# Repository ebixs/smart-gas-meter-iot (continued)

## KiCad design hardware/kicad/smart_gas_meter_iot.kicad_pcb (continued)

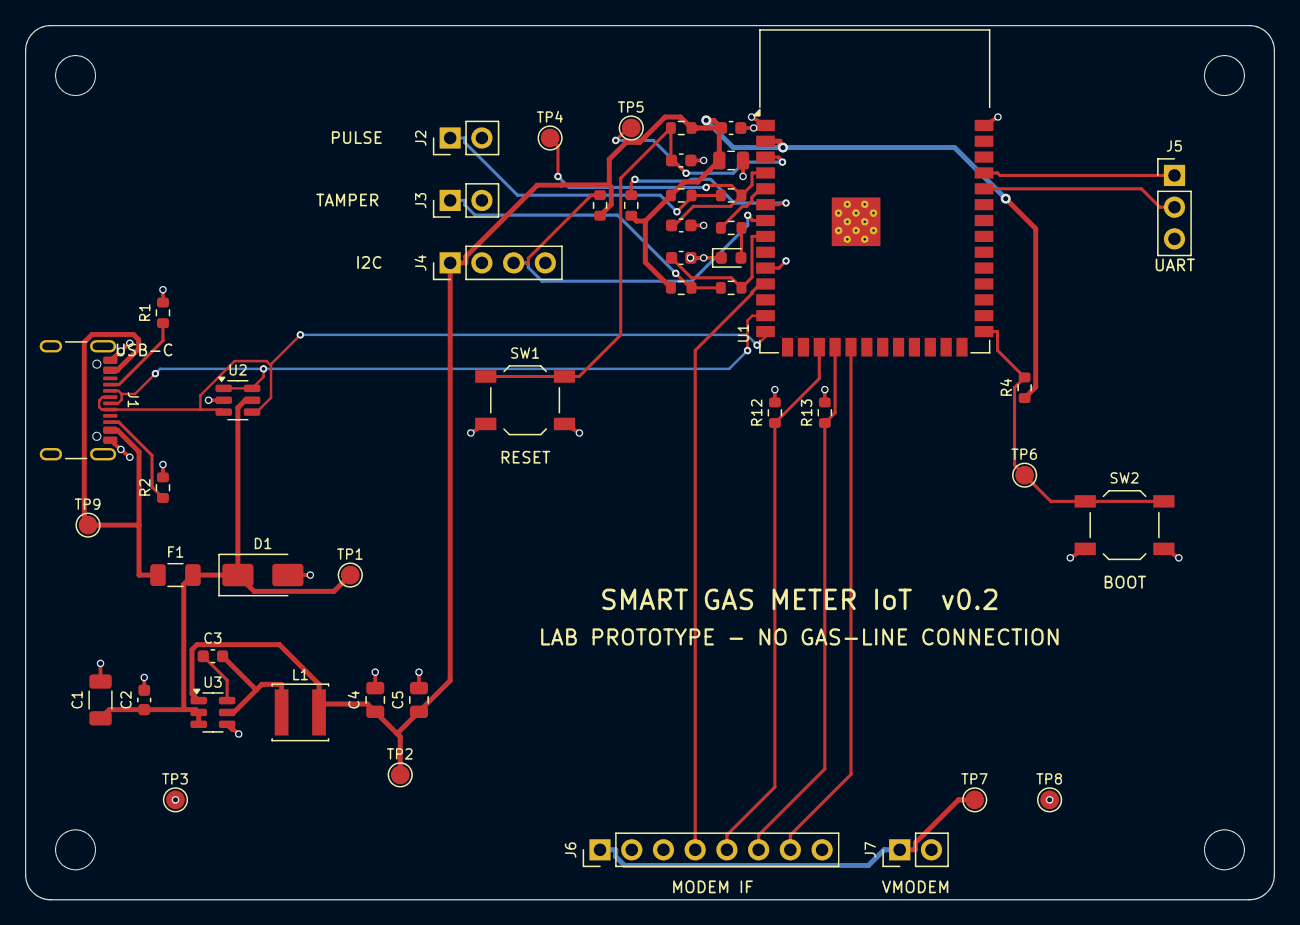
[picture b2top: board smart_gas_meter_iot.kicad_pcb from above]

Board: 4 copper layers, 100.0 x 70.0 mm, 52 parts (0 on the bottom side), 28 nets.

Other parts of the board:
H1, H2, H3, H4: M3; MountingHole_3.2mm_M3

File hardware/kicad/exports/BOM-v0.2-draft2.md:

# BOM — carrier board v0.2-draft2 (generated from `design_v02.py`)

**Candidate BOM — not approved for purchase.** `TBD` / `candidate` entries must be selected and checked against datasheets before freeze.

| Ref | Value | Footprint (SGM lib) | MPN / status | DNP | Note |
|---|---|---|---|---|---|
| J1 | USB-C receptacle (USB 2.0, sink) | `USB_C_Receptacle_GCT_USB4105-xx-A_16P_TopMnt_Horizontal` | GCT USB4105-GF-A (candidate) |  | Footprint/pin map must be checked against the selected connector drawing |
| R1 | 5.1k 1% | `R_0603_1608Metric` | TBD |  | USB-C sink Rd on CC1 |
| R2 | 5.1k 1% | `R_0603_1608Metric` | TBD |  | USB-C sink Rd on CC2 |
| F1 | PTC 0.75A hold, >=6V | `Fuse_1206_3216Metric` | TBD |  | Resettable input protection; size after load budget |
| D1 | TVS 5V standoff (candidate SMAJ5.0CA) | `D_SMA` | SMAJ5.0CA (candidate) |  | VBUS surge clamp after the fuse |
| U2 | USBLC6-2SC6 | `SOT-23-6` | STMicroelectronics USBLC6-2SC6 |  | Low-capacitance USB ESD array; place at the connector |
| U3 | AP63203WU-7 (3.3V buck) | `TSOT-23-6` | Diodes Inc. AP63203WU-7 |  | Fixed 3.3V: FB senses the output; EN tied to VIN (datasheet: auto start-up) |
| C1 | 10uF 25V X7R | `C_1206_3216Metric` | TBD |  | Buck input capacitor (datasheet CIN) |
| C2 | 100nF 50V | `C_0603_1608Metric` | TBD |  | High-frequency input bypass, close to VIN |
| C3 | 100nF 25V | `C_0603_1608Metric` | TBD |  | Bootstrap capacitor between BST and SW (datasheet CBST) |
| L1 | 3.9uH, Isat>=3A (candidate) | `L_Taiyo-Yuden_NR-40xx` | TBD |  | Datasheet table value for 3.3V output |
| C4 | 22uF 10V X7R | `C_0805_2012Metric` | TBD |  | Buck output capacitor 1/2 (datasheet 2x22uF) |
| C5 | 22uF 10V X7R | `C_0805_2012Metric` | TBD |  | Buck output capacitor 2/2 |
| U1 | ESP32-S3-WROOM-1-N8 | `ESP32-S3-WROOM-1` | Espressif ESP32-S3-WROOM-1-N8 |  | Pin numbers per KiCad RF_Module symbol = Espressif datasheet pin table |
| C6 | 10uF 10V X7R | `C_0805_2012Metric` | TBD |  | Module bulk decoupling at the 3V3 pin |
| C7 | 100nF 16V | `C_0603_1608Metric` | TBD |  | Module HF decoupling at the 3V3 pin |
| R3 | 10k | `R_0603_1608Metric` | TBD |  | EN pull-up (Espressif RC delay R=10k) |
| C8 | 1uF 16V | `C_0603_1608Metric` | TBD |  | EN delay capacitor (Espressif RC delay C=1uF) |
| SW1 | RESET | `SW_SPST_TL3342` | TBD |  | Pulls EN low to reset |
| R4 | 10k | `R_0603_1608Metric` | TBD |  | GPIO0 strapping pull-up (run from flash by default) |
| SW2 | BOOT | `SW_SPST_TL3342` | TBD |  | Hold during reset for USB download mode |
| J2 | PULSE_IN (synthetic 3.3V lab signal only) | `PinHeader_1x02_P2.54mm_Vertical` | TBD |  | Max 3.3V logic or dry contact to GND. Never connect a live meter or field wiring |
| R5 | 10k | `R_0603_1608Metric` | TBD |  | Defined idle-high state / dry-contact pull-up |
| R6 | 1k | `R_0603_1608Metric` | TBD |  | Series current limit; place near the MCU pin |
| C9 | 100nF (DNP) | `C_0603_1608Metric` | TBD | yes | Optional RC filter footprint, not fitted by default |
| R7 | 1k | `R_0603_1608Metric` | TBD |  | ~1.3mA with a 2V LED; adjust after LED selection |
| D2 | Green LED | `LED_0603_1608Metric` | TBD |  | Active-high status LED (pin 2 = anode) |
| J3 | TAMPER switch | `PinHeader_1x02_P2.54mm_Vertical` | TBD |  | Enclosure switch closed to GND when lid is closed; open = tamper (advisory only) |
| R8 | 10k | `R_0603_1608Metric` | TBD |  | Pull-up: wire break or lid open reads high |
| R9 | 1k | `R_0603_1608Metric` | TBD |  | Series resistor |
| C10 | 100nF | `C_0603_1608Metric` | TBD |  | Debounce (~1ms with R9) |
| J4 | I2C expansion (3.3V) | `PinHeader_1x04_P2.54mm_Vertical` | TBD |  | Optional 3.3V I2C sensors |
| R10 | 4.7k | `R_0603_1608Metric` | TBD |  | I2C pull-up |
| R11 | 4.7k | `R_0603_1608Metric` | TBD |  | I2C pull-up |
| J5 | Debug UART0 (3.3V) | `PinHeader_1x03_P2.54mm_Vertical` | TBD |  | Pin 1 = module TXD0 output; no power pin to avoid back-feeding |
| J6 | Modem daughterboard interface | `PinHeader_1x08_P2.54mm_Vertical` | TBD |  | 3.3V logic interface; daughterboard provides level translation and modem power design |
| J7 | MODEM_VIN bench supply input | `PinHeader_1x02_P2.54mm_Vertical` | TBD |  | Separate current-limited supply sized to the selected modem; never from +3V3 |
| R12 | 100k | `R_0603_1608Metric` | TBD |  | Modem held disabled while MCU boots |
| R13 | 100k | `R_0603_1608Metric` | TBD |  | Reset de-asserted by default (polarity per modem) |
| TP1 | TP_5V | `TestPoint_Pad_D1.5mm` | TBD |  |  |
| TP2 | TP_3V3 | `TestPoint_Pad_D1.5mm` | TBD |  |  |
| TP3 | TP_GND | `TestPoint_Pad_D1.5mm` | TBD |  |  |
| TP4 | TP_PULSE | `TestPoint_Pad_D1.5mm` | TBD |  |  |
| TP5 | TP_EN | `TestPoint_Pad_D1.5mm` | TBD |  |  |
| TP6 | TP_BOOT | `TestPoint_Pad_D1.5mm` | TBD |  |  |
| TP7 | TP_VMODEM | `TestPoint_Pad_D1.5mm` | TBD |  |  |
| TP8 | TP_GND2 | `TestPoint_Pad_D1.5mm` | TBD |  |  |
| TP9 | TP_VBUS | `TestPoint_Pad_D1.5mm` | TBD |  |  |

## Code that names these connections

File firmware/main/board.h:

/*
 * GPIO map of the v0.2 board (hardware/kicad/design_v02.py, U1 = ESP32-S3-WROOM-1).
 * Module pin -> GPIO per the Espressif WROOM-1 datasheet pin table.
 * tests/test_firmware_core.py checks this file against the design source.
 */
#ifndef SGM_BOARD_H
#define SGM_BOARD_H

#include "driver/gpio.h"

#define SGM_GPIO_PULSE_IN      GPIO_NUM_4   /* module pin 4,  net PULSE_IN (10k pull-up, 1k series) */
#define SGM_GPIO_LED           GPIO_NUM_5   /* module pin 5,  net LED_DRV (active high) */
#define SGM_GPIO_I2C_SDA       GPIO_NUM_6   /* module pin 6,  net I2C_SDA */
#define SGM_GPIO_I2C_SCL       GPIO_NUM_7   /* module pin 7,  net I2C_SCL */
#define SGM_GPIO_TAMPER_IN     GPIO_NUM_15  /* module pin 8,  net TAMPER_IN (high = lid open / wire cut) */
#define SGM_GPIO_MODEM_TXD     GPIO_NUM_17  /* module pin 10, net MODEM_TXD (MCU -> modem) */
#define SGM_GPIO_MODEM_RXD     GPIO_NUM_18  /* module pin 11, net MODEM_RXD (modem -> MCU) */
#define SGM_GPIO_MODEM_EN      GPIO_NUM_9   /* module pin 17, net MODEM_EN (100k pull-down: off at boot) */
#define SGM_GPIO_MODEM_RESET   GPIO_NUM_10  /* module pin 18, net MODEM_RESET (100k pull-down) */
#define SGM_GPIO_MODEM_STATUS  GPIO_NUM_11  /* module pin 19, net MODEM_STATUS (input) */

#define SGM_MODEM_UART         UART_NUM_1

#endif

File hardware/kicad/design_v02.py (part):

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    Part("SW1", "SW_Push", "RESET", "SW_SPST_TL3342", (134.62, 162.56),
         {"1": "MCU_EN", "2": "GND"}, "mcu", "Pulls EN low to reset"),
    Part("R4", "R", "10k", "R_0603_1608Metric", (119.38, 129.54),
         {"1": "+3V3", "2": "BOOT_N"}, "mcu", "GPIO0 strapping pull-up (run from flash by default)"),
    Part("SW2", "SW_Push", "BOOT", "SW_SPST_TL3342", (106.68, 175.26),
         {"1": "BOOT_N", "2": "GND"}, "mcu", "Hold during reset for USB download mode"),

    # ------------------------------------------------------------------ 4. Synthetic pulse input
    Part("J2", "Conn_01x02", "PULSE_IN (synthetic 3.3V lab signal only)", "PinHeader_1x02_P2.54mm_Vertical",
         (279.4, 50.8), {"1": "PULSE_EXT", "2": "GND"}, "pulse",
         "Max 3.3V logic or dry contact to GND. Never connect a live meter or field wiring"),
    Part("R5", "R", "10k", "R_0603_1608Metric", (330.2, 43.18),
         {"1": "+3V3", "2": "PULSE_EXT"}, "pulse", "Defined idle-high state / dry-contact pull-up"),
    Part("R6", "R", "1k", "R_0603_1608Metric", (345.44, 63.5),
         {"1": "PULSE_EXT", "2": "PULSE_IN"}, "pulse", "Series current limit; place near the MCU pin"),
    Part("C9", "C", "100nF (DNP)", "C_0603_1608Metric", (360.68, 76.2),
         {"1": "PULSE_IN", "2": "GND"}, "pulse", "Optional RC filter footprint, not fitted by default", dnp=True),

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    Part("R7", "R", "1k", "R_0603_1608Metric", (279.4, 121.92),
         {"1": "LED_DRV", "2": "LED_A"}, "status", "~1.3mA with a 2V LED; adjust after LED selection"),
    Part("D2", "LED", "Green LED", "LED_0603_1608Metric", (302.26, 134.62),
         {"2": "LED_A", "1": "GND"}, "status", "Active-high status LED (pin 2 = anode)"),

    # ------------------------------------------------------------------ 6. Tamper input
    Part("J3", "Conn_01x02", "TAMPER switch", "PinHeader_1x02_P2.54mm_Vertical", (279.4, 172.72),
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         {"1": "MODEM_VIN", "2": "GND", "3": "MODEM_TXD", "4": "MODEM_RXD",
          "5": "MODEM_EN", "6": "MODEM_RESET", "7": "MODEM_STATUS", "8": "GND"}, "modem",
         "3.3V logic interface; daughterboard provides level translation and modem power design"),
    Part("J7", "Conn_01x02", "MODEM_VIN bench supply input", "PinHeader_1x02_P2.54mm_Vertical", (30.48, 220.98),
         {"1": "MODEM_VIN", "2": "GND"}, "modem",
         "Separate current-limited supply sized to the selected modem; never from +3V3"),
    Part("R12", "R", "100k", "R_0603_1608Metric", (129.54, 220.98),
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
